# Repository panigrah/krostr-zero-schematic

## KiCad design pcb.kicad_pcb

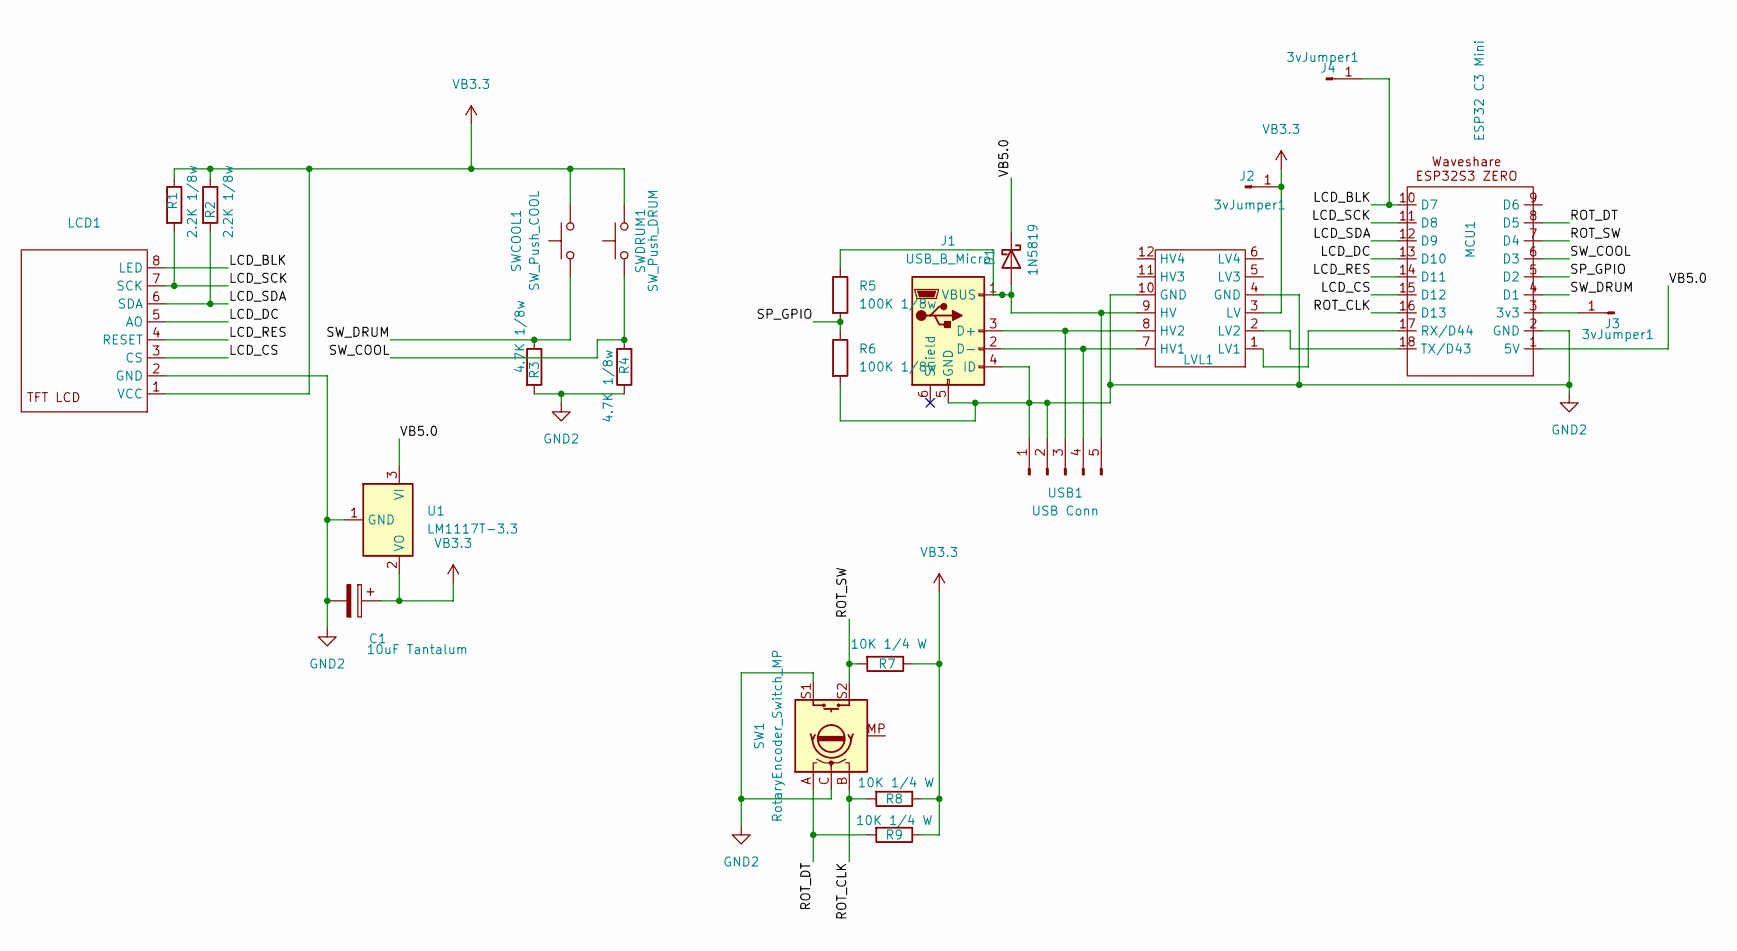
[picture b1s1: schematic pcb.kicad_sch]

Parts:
C1: 10uF Tantalum; CP_Radial_Tantal_D4.5mm_P2.50mm
D1: 1N5819; D_DO-41_SOD81_P7.62mm_Horizontal
J1: USB_B_Micro; USB Micro 5P
J2, J3, J4: 3vJumper1; PinHeader_1x01_P2.54mm_Vertical
LCD1: ST3375_TFT_120x160
LVL1: Bidirectional Level Shifter 4x
MCU1: ESP32 C3 Mini; ESP32S3 Zero Waveshare
R1, R2: 2.2K 1/8w; R_Axial_DIN0204_L3.6mm_D1.6mm_P7.62mm_Horizontal
R3, R4: 4.7K 1/8w; R_Axial_DIN0204_L3.6mm_D1.6mm_P7.62mm_Horizontal
R5, R6: 100K 1/8w; R_Axial_DIN0204_L3.6mm_D1.6mm_P7.62mm_Horizontal
R7, R8, R9: 10K 1/4 W; R_Axial_DIN0204_L3.6mm_D1.6mm_P5.08mm_Horizontal
SW1: RotaryEncoder_Switch_MP; RotaryEncoder_Alps_EC12E-Switch_Vertical_H20mm_CircularMoun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
SWCOOL1: SW_Push_COOL; SW_PUSH_6mm
SWDRUM1: SW_Push_DRUM; SW_PUSH_6mm
U1: LM1117T-3.3; TO-220-3_Vertical
USB1: USB Conn; JST_EH_B5B-EH-A_1x05_P2.50mm_Vertical

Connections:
/LCD_BLK: J4.1, LCD1.8 (LED), MCU1.10 (D7)
/LCD_CS: LCD1.3 (CS), MCU1.15 (D12)
/LCD_DC: LCD1.5 (AO), MCU1.13 (D10)
/LCD_RES: LCD1.4 (RESET), MCU1.14 (D11)
/LCD_SCK: LCD1.7 (SCK), MCU1.11 (D8), R1.2
/LCD_SDA: LCD1.6 (SDA), MCU1.12 (D9), R2.2
/ROT_CLK: MCU1.16 (D13), R8.2, SW1.B
/ROT_DT: MCU1.8 (D5), R9.2, SW1.A
/ROT_SW: MCU1.7 (D4), R7.2, SW1.S2
/SP_GPIO: MCU1.5 (D2), R5.2, R6.1
/SW_COOL: MCU1.6 (D3), R4.2, SWDRUM1.1
/SW_DRUM: MCU1.4 (D1), R3.1, SWCOOL1.1
/VB5.0: D1.1 (K), MCU1.1 (5V), U1.3 (VI)
GND2: C1.2, J1.4 (ID), J1.5 (GND), LCD1.2 (GND), LVL1.4 (GND), LVL1.10 (GND), MCU1.2 (GND), R3.2, R4.1, R6.2, SW1.C, SW1.S1, U1.1 (GND), USB1.1, USB1.2
unnamed: D1.2 (A), J1.1 (VBUS), LVL1.9 (HV), R5.1, USB1.5
unnamed: J1.3 (D+), LVL1.8 (HV2), USB1.3
unnamed: J1.2 (D-), LVL1.7 (HV1), USB1.4
unnamed: J3.1, MCU1.3 (3v3)
unnamed: LVL1.1 (LV1), MCU1.17 (RX/D44)
unnamed: LVL1.2 (LV2), MCU1.18 (TX/D43)
VB3.3: C1.1, J2.1, LCD1.1 (VCC), LVL1.3 (LV), R1.1, R2.1, R7.1, R8.1, R9.1, SWCOOL1.2, SWDRUM1.2, U1.2 (VO)

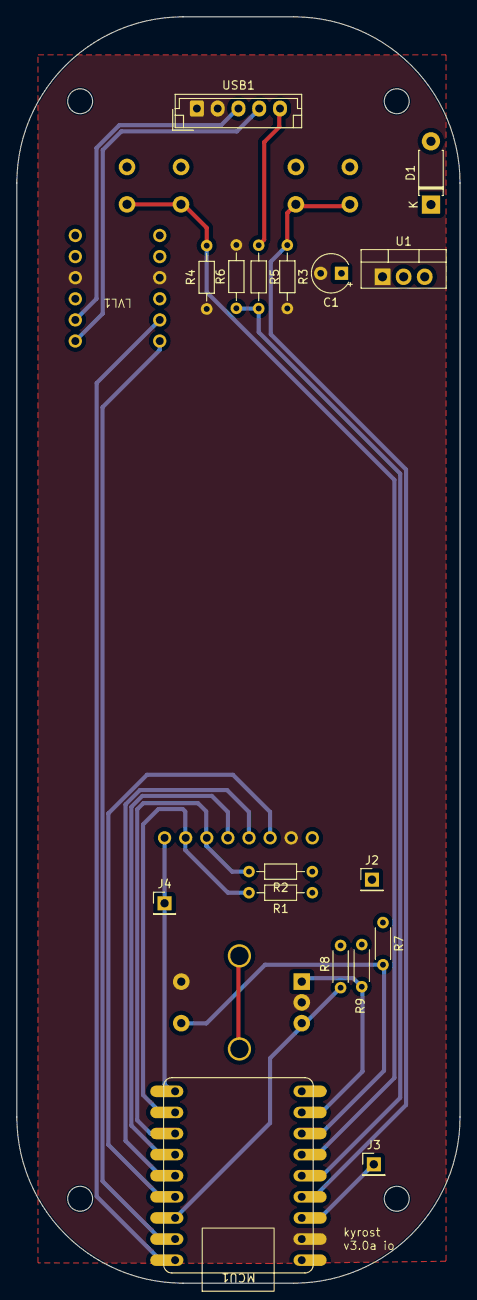
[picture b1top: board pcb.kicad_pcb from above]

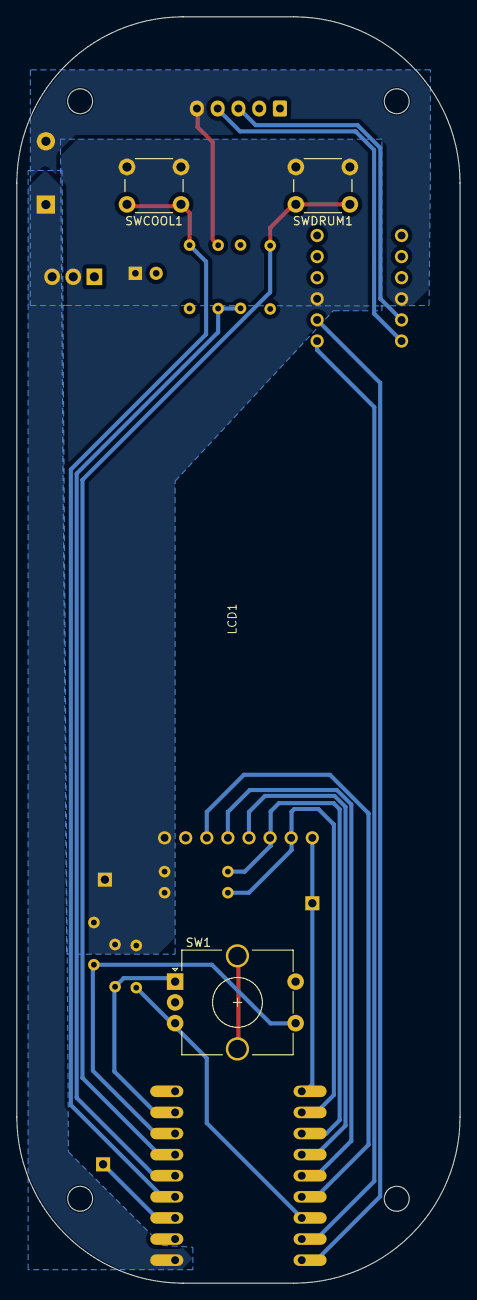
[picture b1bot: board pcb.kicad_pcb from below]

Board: 2 copper layers, 53.3 x 152.4 mm, 22 parts (4 on the bottom side), 21 nets.

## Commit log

2025-03-01 initial version
2025-03-01 updated to support both c3 mini and a c3/S3 zero
2025-03-03 minor updates
